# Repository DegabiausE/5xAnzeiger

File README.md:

# 5xAnzeiger
Projekt um den Umgang mit grafischen Displays zu lernen. 
Nebenbei auch um Werte der Solaranlage aus Homeassistant anzuzeigen.

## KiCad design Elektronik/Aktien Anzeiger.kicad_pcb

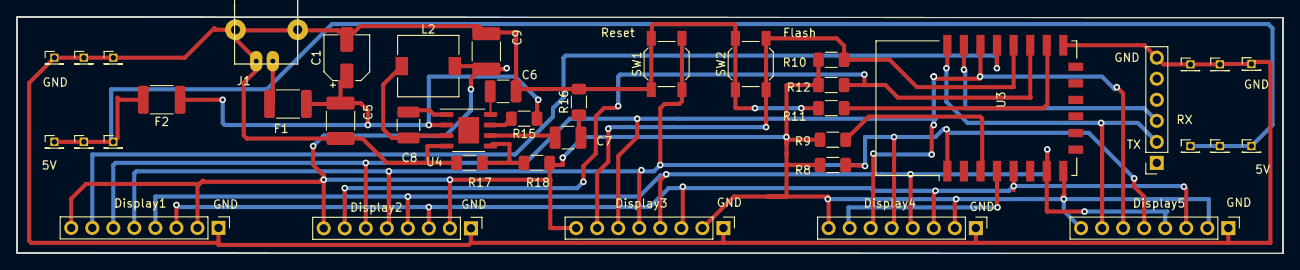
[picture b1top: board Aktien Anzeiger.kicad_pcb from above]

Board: 2 copper layers, 152.9 x 28.5 mm, 41 parts (0 on the bottom side), 24 nets.

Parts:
C1: 22µF; CP_Elec_5x5.7
C5, C9: 22µF; C_1812_4532Metric_Pad1.57x3.40mm_HandSolder
C6: 100nF; C_1210_3225Metric_Pad1.33x2.70mm_HandSolder
C7: 3.9nF; C_1210_3225Metric_Pad1.33x2.70mm_HandSolder
C8: 10nF; C_1210_3225Metric_Pad1.33x2.70mm_HandSolder
Display1, Display2, Display3, Display4, Display5: PinHeader_1x08_P2.54mm_Vertical
F1, F2: MSMD050-15V; Fuse_1812_4532Metric_Pad1.30x3.40mm_HandSolder
J1: USB_B_Micro_Power_Only; USB_Micro-B_Power_Only
J2, J4, J5, J6, J7, J8: +; PinHeader_1x01_P1.27mm_Vertical
J3: Conn_01x06_Female; PinSocket_1x06_P2.54mm_Vertical
J9, J10, J11, J12, J13, J14: -; PinHeader_1x01_P1.27mm_Vertical
L2: 10µH; L_7.3x7.3_H4.5
R8, R9, R10, R11, R12: 10k; R_1206_3216Metric_Pad1.30x1.75mm_HandSolder
R15: 100K; R_1206_3216Metric_Pad1.30x1.75mm_HandSolder
R16: 6,8K; R_1206_3216Metric_Pad1.30x1.75mm_HandSolder
R17: 22k; R_1206_3216Metric_Pad1.30x1.75mm_HandSolder
R18: 56k; R_1206_3216Metric_Pad1.30x1.75mm_HandSolder
SW1: Reset; SW_SPST_SKQG_WithStem
SW2: Flash; SW_SPST_SKQG_WithStem
U3: ESP-12F; ESP-12E-Stefan
U4: MP2307; SOIC-8-1EP_3.9x4.9mm_P1.27mm_EP2.514x3.2mm

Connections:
/ESP8266/3V3: C9.2, Display1.2 (VCC), Display1.8 (BLK), Display2.2 (VCC), Display2.8 (BLK), Display3.2 (VCC), Display3.8 (BLK), Display4.2 (VCC), Display4.8 (BLK), Display5.2 (VCC), Display5.8 (BLK), L2.2, R8.2, R9.2, R10.1, R12.1, R18.2, U3.8 (VCC)
/ESP8266/D0: Display4.7 (CS), U3.4 (GPIO16)
/ESP8266/D1: Display1.6 (DC), Display2.6 (DC), Display3.6 (DC), Display4.6 (DC), Display5.6 (DC), U3.20 (GPIO5)
/ESP8266/D2: Display1.7 (CS), U3.19 (GPIO4)
/ESP8266/D3: Display3.7 (CS), R10.2, SW2.2, U3.18 (GPIO0)
/ESP8266/D4: Display2.7 (CS), R12.2, U3.17 (GPIO2)
/ESP8266/D5: Display1.3 (SCL), Display2.3 (SCL), Display3.3 (SCL), Display4.3 (SCL), Display5.3 (SCL), U3.5 (GPIO14)
/ESP8266/D7: Display1.4 (SDA), Display2.4 (SDA), Display3.4 (SDA), Display4.4 (SDA), Display5.4 (SDA), U3.7 (GPIO13)
/ESP8266/D8: R11.2, U3.16 (GPIO15)
/ESP8266/D9: J3.3, U3.21 (GPIO3/RXD)
/ESP8266/D10: Display5.7 (CS), J3.2, U3.22 (GPIO1/TXD)
/ESP8266/RST: Display1.5 (RES), Display2.5 (RES), Display3.5 (RES), Display4.5 (RES), Display5.5 (RES), R8.1, SW1.2, U3.1 (~RST)
/Power/Vcc5: C1.1, C5.1, F1.2, F2.1, R15.1, U4.2 (IN)
Gnd: C1.2, C5.2, C6.2, C9.1, Display1.1 (Gnd), Display2.1 (Gnd), Display3.1 (Gnd), Display4.1 (Gnd), Display5.1 (Gnd), J1.4 (Gnd), J1.6 (Shield), J3.6, J9.1, J10.1, J11.1, J12.1, J13.1, J14.1, R11.1, R16.2, R17.1, SW1.1, SW2.1, U3.15 (GND), U4.4 (GND)
unnamed: C7.1, R16.1
unnamed: F1.1, J1.1 (+)
unnamed: F2.2, J2.1, J4.1, J5.1, J6.1, J7.1, J8.1
unnamed: R9.1, U3.3 (EN)
unnamed: C8.1, U4.1 (BS)
unnamed: C7.2, U4.6 (COMP)
unnamed: R15.2, U4.7 (EN)
unnamed: R17.2, R18.1, U4.5 (FB)
unnamed: C6.1, U4.8 (SS)
unnamed: C8.2, L2.1, U4.3 (SW)

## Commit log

2024-09-09 Create Software
2024-09-09 inital
